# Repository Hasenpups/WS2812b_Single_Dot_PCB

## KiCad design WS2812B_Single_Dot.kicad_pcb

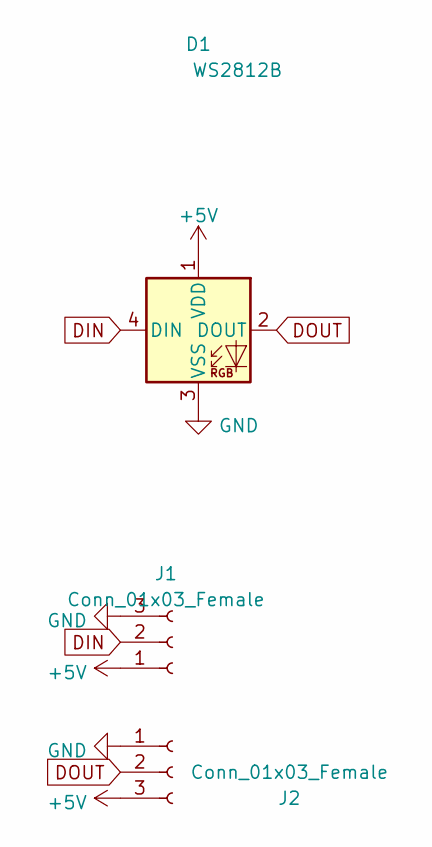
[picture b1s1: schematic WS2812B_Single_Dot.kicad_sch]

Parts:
D1: WS2812B; LED_WS2812B_PLCC4_5.0x5.0mm_P3.2mm
J1, J2: Conn_01x03_Female; PinHeader_1x03_P2.54mm_Horizontal

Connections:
+5V: D1.1 (VDD), J1.1, J2.3
DIN: D1.4 (DIN), J1.2
DOUT: D1.2 (DOUT), J2.2
GND: D1.3 (VSS), J1.3, J2.1

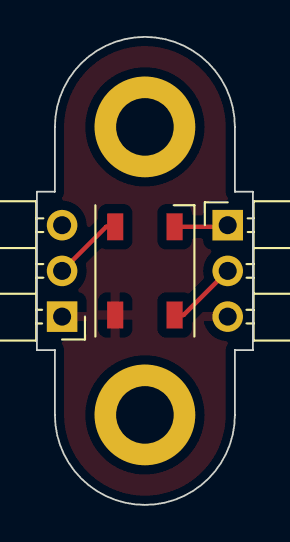
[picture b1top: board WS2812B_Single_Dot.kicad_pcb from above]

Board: 2 copper layers, 12.0 x 26.0 mm, 3 parts (0 on the bottom side), 4 nets.

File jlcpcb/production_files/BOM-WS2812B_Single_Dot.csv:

Comment,Designator,Footprint,LCSC
WS2812B,D1,LED_WS2812B_PLCC4_5.0x5.0mm_P3.2mm,C2843785
Conn_01x03_Female,J1,PinHeader_1x03_P2.54mm_Horizontal,
Conn_01x03_Female,J2,PinHeader_1x03_P2.54mm_Horizontal,

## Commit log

2023-01-06 - initial commit
2023-01-19 - add JLCPCB files
